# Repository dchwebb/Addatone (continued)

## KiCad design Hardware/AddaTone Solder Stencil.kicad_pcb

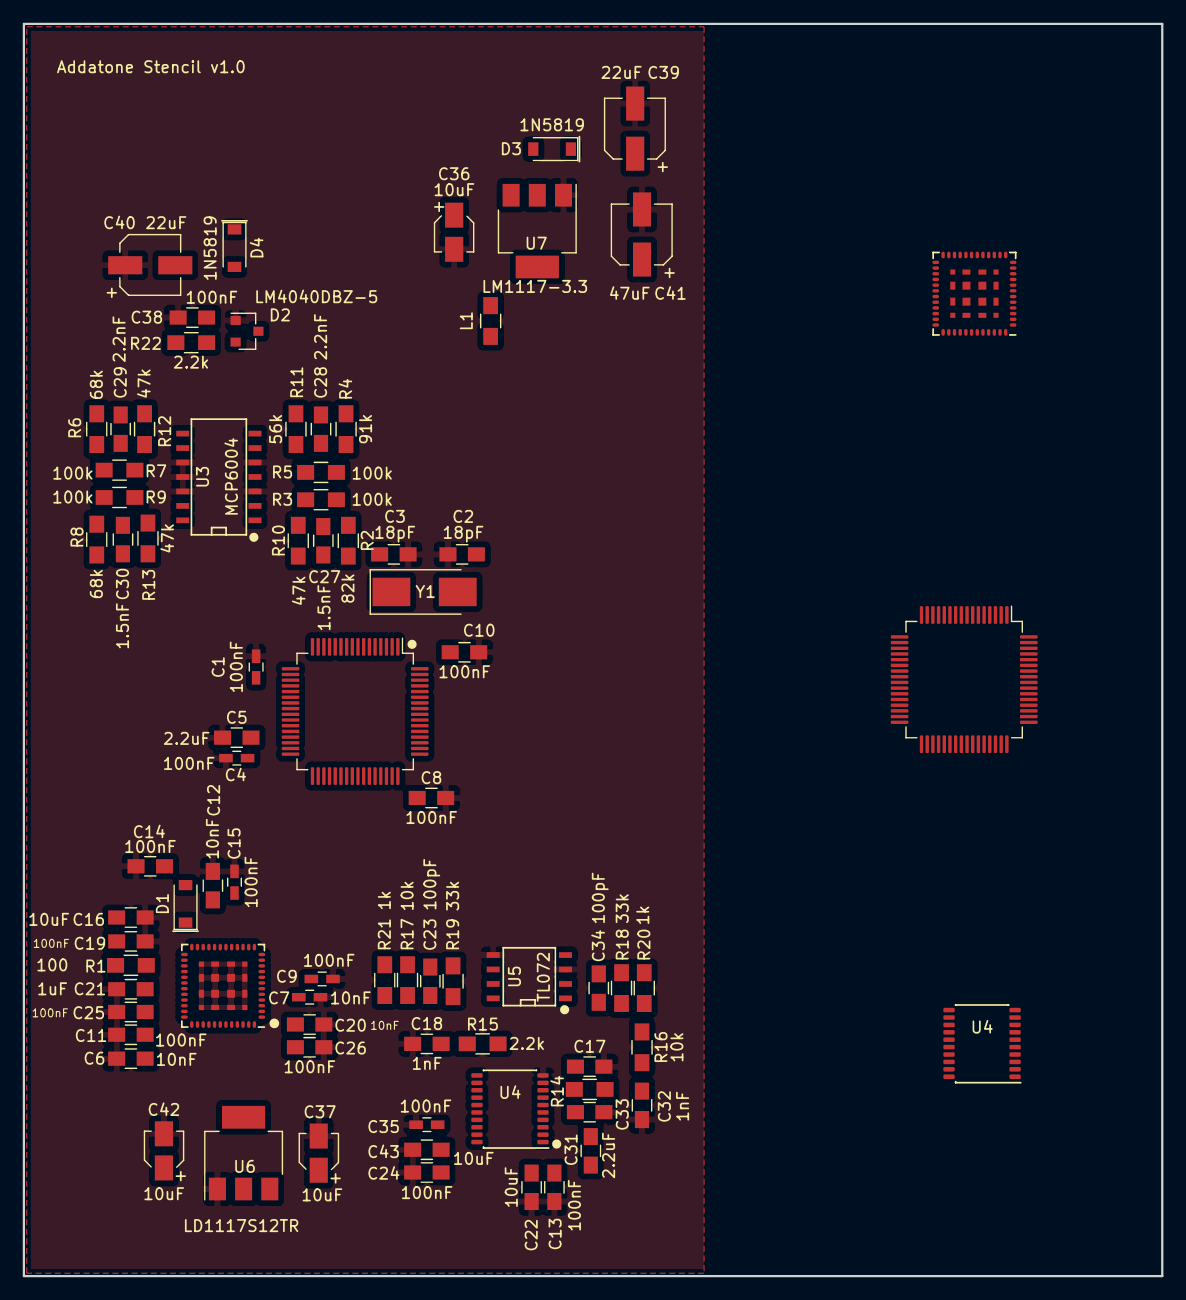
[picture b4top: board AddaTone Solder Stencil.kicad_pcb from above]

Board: 2 copper layers, 100.0 x 110.0 mm, 81 parts (0 on the bottom side), 110 nets, no tracks yet.

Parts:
C1, C4, C9, C15, C35: 100nF; C_0603_HandSoldering
C2, C3: 18pF; C_0805_HandSoldering
C5, C31, C33: 2.2uF; C_0805_HandSoldering
C6, C12, C20: 10nF; C_0805_HandSoldering
C7: 10nF; C_0603_HandSoldering
C8, C10, C11, C13, C14, C17, C19, C24, C25, C26, C38: 100nF; C_0805_HandSoldering
C16, C22, C43: 10uF; C_0805_HandSoldering
C18, C32: 1nF; C_0805_HandSoldering
C21: 1uF; C_0805_HandSoldering
C23, C34: 100pF; C_0805_HandSoldering
C27, C30: 1.5nF; C_0805_HandSoldering
C28, C29: 2.2nF; C_0805_HandSoldering
C36, C37, C42: 10uF; CP_Elec_3x5.3
C39, C40: 22uF; CP_Elec_5x5.3
C41: 47uF; CP_Elec_5x5.3
D1: MBR130T1G; D_SOD-123
D2: LM4040DBZ-5; SOT-23
D3, D4: 1N5819; D_SOD-123
L1: L; L_0805_HandSoldering
R1: 100; R_0805_HandSoldering
R2: 82k; R_0805_HandSoldering
R3, R5, R7, R9: 100k; R_0805_HandSoldering
R4: 91k; R_0805_HandSoldering
R6, R8: 68k; R_0805_HandSoldering
R10, R12, R13: 47k; R_0805_HandSoldering
R11: 56k; R_0805_HandSoldering
R14, R15, R22: 2.2k; R_0805_HandSoldering
R16, R17: 10k; R_0805_HandSoldering
R18, R19: 33k; R_0805_HandSoldering
R20, R21: 1k; R_0805_HandSoldering
U1, U1#2: STM32F446RETx; LQFP-64_10x10mm_P0.5mm
U2, U2#2: ICE40UP5K-SG48ITR; ICE40_QFN-48-stencil
U3: MCP6004; SOIC-14_N
U4, U4#2: PCM5100APW; SSOP-20_4.4x6.5mm_Pitch0.65mm_Round_Pads
U5: TL072; SOIC-8-N
U6: LD1117S12TR; SOT-223
U7: LM1117-3.3; SOT-223
Y1: ECS-12MHz; Crystal_SMD_0603-2pin_6.0x3.5mm_HandSoldering

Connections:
+1V2: C7.1, C9.1, C16.1, C19.1, C21.1, C25.1, C42.1, R1.1, U2.5, U2.30, U2#2.5, U2#2.30, U6.2
+3.3VA: C13.1, C17.1, C22.1, L1.1, U1.13, U1#2.13, U3.4, U4.1, U4.8, U4#2.1, U4#2.8
ADC_CS: U1.50, U1#2.50, U2.10, U2#2.10
ADC_Clock: U1.55, U1#2.55, U2.9, U2#2.9
ADC_Data: U1.57, U1#2.57, U2.6, U2#2.6
AREF_-5: C38.1, D2.2, R2.2, R4.2, R6.2, R8.2, R22.2
CTUNE: U1.27, U1#2.27
Calibration: U1.2, U1#2.2
DAC1_OUT: R14.2, U4.6, U4#2.6
DAC2_OUT: R15.2, U4.7, U4#2.7
DAC_BCLK: U2.4, U2#2.4, U4.13, U4#2.13
DAC_DATA: U2.3, U2#2.3, U4.14, U4#2.14
DAC_LRCLK: U2.48, U2#2.48, U4.15, U4#2.15
FPGA_DONE: U1.42, U1#2.42, U2.7, U2#2.7
FPGA_RESET: U1.38, U1#2.38, U2.8, U2#2.8
FPGA_SCK: U1.34, U1#2.34, U2.15, U2#2.15
FPGA_SI: U1.36, U1#2.36, U2.17, U2#2.17
FPGA_SO: U2.14, U2#2.14
FPGA_SS: U1.33, U1#2.33, U2.16, U2#2.16
FTUNE: U1.25, U1#2.25
F_TEST1: U2.42, U2#2.42
F_TEST2: U2.45, U2#2.45
GND: C1.2, C2.2, C3.2, C4.2, C5.1, C6.2, C7.2, C8.2, C9.2, C10.2, C11.2, C12.2, C13.2, C14.1, C15.2, C16.2, C17.2, C18.1, C19.2, C20.2, C21.2, C22.2, C24.2, C25.2, C26.2, C32.1, C33.2, C35.1, C36.2, C37.2, C38.2, C39.2, C40.1, C41.2, C42.2, C43.2, D2.1, U1.12, U1.18, U1.31, U1.47, U1.60, U1.63, U1#2.12, U1#2.18, U1#2.31, U1#2.47, U1#2.60, U1#2.63, U2.49, U2#2.49, U3.3, U3.5, U3.10, U3.11, U3.12, U4.3, U4.9, U4.10, U4.12, U4.16, U4.19, U4#2.3, U4#2.9, U4#2.10, U4#2.12, U4#2.16, U4#2.19, U5.3, U5.5, U6.1, U7.1
HARM1_CV: C28.2, R11.1, U1.11, U1#2.11, U3.7
HARM1_POT: U1.26, U1#2.26
HARM2_CV: C29.2, R12.1, U1.17, U1#2.17, U3.8
HARM2_POT: U1.10, U1#2.10
HARM_COUNT_POT: U1.16, U1#2.16
MCO2_CLOCK_OUT: U1.40, U1#2.40, U2.20, U2#2.20
MIX_SWITCH: U2.37, U2#2.37
unnamed: C2.1, U1.5, U1#2.5, Y1.2
unnamed: C3.1, U1.6, U1#2.6, Y1.1
unnamed: C5.2, U1.30, U1#2.30
unnamed: C18.2, R15.1, R17.2
unnamed: C23.1, R17.1, R19.2, U5.6
unnamed: C23.2, R19.1, R21.2, U5.7
unnamed: C27.1, R2.1, R3.1, R10.2, U3.2
unnamed: C28.1, R4.1, R5.1, R11.2, U3.6
unnamed: C29.1, R6.1, R7.1, R12.2, U3.9
unnamed: C30.1, R8.1, R9.1, R13.2, U3.13
unnamed: C31.1, U4.2, U4#2.2
unnamed: C31.2, U4.4, U4#2.4
unnamed: C32.2, R14.1, R16.2
unnamed: C33.1, U4.5, U4#2.5
unnamed: C34.1, R16.1, R18.2, U5.2
unnamed: C34.2, R18.1, R20.2, U5.1
unnamed: C35.2, U4.18, U4#2.18
unnamed: D1.1, U2.24, U2#2.24
unnamed: R1.2, U2.29, U2#2.29
unnamed: U1.1, U1#2.1
unnamed: U1.3, U1#2.3
unnamed: U1.4, U1#2.4
unnamed: U1.9, U1#2.9
unnamed: U1.14, U1#2.14
unnamed: U1.15, U1#2.15
unnamed: U1.20, U1#2.20
unnamed: U1.21, U1#2.21
unnamed: U1.24, U1#2.24
unnamed: U1.28, U1#2.28
unnamed: U1.29, U1#2.29
unnamed: U1.35, U1#2.35
unnamed: U1.37, U1#2.37
unnamed: U1.39, U1#2.39
unnamed: U1.41, U1#2.41
unnamed: U1.43, U1#2.43
unnamed: U1.44, U1#2.44
unnamed: U1.45, U1#2.45
unnamed: U1.51, U1#2.51
unnamed: U1.52, U1#2.52
unnamed: U1.53, U1#2.53
unnamed: U1.54, U1#2.54
unnamed: U1.56, U1#2.56
unnamed: U1.58, U1#2.58
unnamed: U1.59, U1#2.59
unnamed: U1.61, U1#2.61
unnamed: U1.62, U1#2.62
unnamed: U2.2, U2#2.2
unnamed: U2.11, U2#2.11
unnamed: U2.12, U2#2.12
unnamed: U2.13, U2#2.13
unnamed: U2.18, U2#2.18
unnamed: U2.19, U2#2.19
unnamed: U2.21, U2#2.21
unnamed: U2.23, U2#2.23
unnamed: U2.26, U2#2.26
unnamed: U2.27, U2#2.27
unnamed: U2.28, U2#2.28
unnamed: U2.31, U2#2.31
unnamed: U2.32, U2#2.32
unnamed: U2.34, U2#2.34
unnamed: U2.35, U2#2.35
unnamed: U2.36, U2#2.36
unnamed: U2.38, U2#2.38
unnamed: U2.39, U2#2.39
unnamed: U2.40, U2#2.40
unnamed: U2.41, U2#2.41
unnamed: U2.43, U2#2.43
unnamed: U2.44, U2#2.44
unnamed: U2.46, U2#2.46
unnamed: U2.47, U2#2.47
PITCH_CV: C27.2, R10.1, U1.22, U1#2.22, U3.1
RESET: U1.7, U1#2.7
RING_MOD: U2.25, U2#2.25
SWCLK: U1.49, U1#2.49
SWDIO: U1.46, U1#2.46
VCC: C36.1, C37.1, C39.1, D3.1, U5.8, U6.3, U7.3
VCCIO_0: C1.1, C4.1, C6.1, C8.1, C10.1, C11.1, C12.1, C14.2, C15.1, C20.1, C24.1, C26.1, C41.1, C43.1, D1.2, L1.2, U1.19, U1.32, U1.48, U1.64, U1#2.19, U1#2.32, U1#2.48, U1#2.64, U2.1, U2.22, U2.33, U2#2.1, U2#2.22, U2#2.33, U4.11, U4.17, U4.20, U4#2.11, U4#2.17, U4#2.20, U7.2
VEE: C40.2, D4.2, R22.1, U5.4
WARP_CV: C30.2, R13.1, U1.23, U1#2.23, U3.14
WARP_POT: U1.8, U1#2.8

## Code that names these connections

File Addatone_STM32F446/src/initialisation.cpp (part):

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void InitHardware()
{
	InitClocks();
	InitMCO2();									// Initialise output of HSE oscillator on pin PC9
	InitSysTick();
	InitIO();
	InitFPGAProg();								// Initialise SPI peripheral used to program bitstream into FPGA
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
void InitMCO2()
{
	// Initialise oscillator output on MCO2 pin PC9
	RCC->AHB1ENR |= RCC_AHB1ENR_GPIOCEN;
	GPIOC->MODER |= GPIO_MODER_MODER9_1;			// Set PC9 to Alternate function mode (0b10); Uses alternate function AF0 so set by default

	RCC->CFGR |= RCC_CFGR_MCO2_1; 					// 00: System clock; 01: PLLI2S clock; 10: HSE; 11: PLL clock
}
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

	/* 446:
	0	PITCH_CV		PA6
	1	HARM1_CV		PC3
	2	HARM2_CV		PA3
	3	FREQ_SCALE_CV	PA7
	4	HARM_COUNT_POT	PA2
	5	CTUNE			PB1
	6	FTUNE			PC5
	7	HARM1_POT		PB0
	8	HARM2_POT		PC2
	9	FREQ_SC_POT		PC0
	*/

	ADC2->CR1 |= ADC_CR1_SCAN;						// Activate scan mode
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	//	Enable GPIO and SPI clocks
	RCC->APB1ENR |= RCC_APB1ENR_SPI2EN;

	GpioPin::Init(GPIOB, 15, GpioPin::Type::AlternateFunction, 5, GpioPin::DriveStrength::VeryHigh);	// PB15: SPI_MOSI [alternate function AF5] to ICE_MOSI
	GpioPin::Init(GPIOB, 13, GpioPin::Type::AlternateFunction, 5, GpioPin::DriveStrength::VeryHigh);		// PB13: SPI_SCK [alternate function AF5]
	GpioPin::Init(GPIOB, 12, GpioPin::Type::Output);			// PB12 Software NSS
	GpioPin::SetHigh(GPIOB, 12);

	// PC7 Reset FPGA - configure as Open drain. This will only pull pin low when set to 0; otherwise output is high impedence
	RCC->AHB1ENR |= RCC_AHB1ENR_GPIOCEN;			// reset and clock control - advanced high performance bus - GPIO port C
	GPIOC->OTYPER |= GPIO_OTYPER_OT7;				// Configure as open drain
	GPIOC->BSRR |= GPIO_BSRR_BS_7;
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{
	RCC->APB1ENR |= RCC_APB1ENR_SPI3EN;				//	Enable SPI clock

	GpioPin::Init(GPIOB, 5, GpioPin::Type::AlternateFunction, 6, GpioPin::DriveStrength::VeryHigh);		// PB5 (57): SPI_MOSI [AF6]
	GpioPin::Init(GPIOB, 3, GpioPin::Type::AlternateFunction, 6, GpioPin::DriveStrength::VeryHigh);		// PB3 (55) SPI_SCK [AF6]
	GpioPin::Init(GPIOA, 15, GpioPin::Type::Output);													// PA15 (50) Software NSS
	GpioPin::SetHigh(GPIOA, 15);

	// Configure SPI
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void InitI2S()
{
	/* All AF5
	PC3 I2S2_SD
	PC6 I2S2_MCK
	[PC9 I2S_CKIN]

	62 PB9 I2S2_WS
	PB10 I2S2_CK
	33 PB12 I2S2_WS
	34 PB13 I2S2_CK
	[PB14 I2S2ext_SD]
	36 PB15 I2S2_SD

	*/
	//	Enable GPIO and SPI clocks
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	RCC->APB1ENR |= RCC_APB1ENR_SPI2EN;

/*
	// PB12: I2S2_WS [alternate function AF5]
	GPIOB->MODER |= GPIO_MODER_MODER12_1;			// 00: Input (reset state)	01: General purpose output mode	10: Alternate function mode	11: Analog mode
	GPIOB->OSPEEDR |= GPIO_OSPEEDER_OSPEEDR12;		// V High  - 00: Low speed; 01: Medium speed; 10: High speed; 11: Very high speed
	GPIOB->AFR[1] |= 0b0101 << 16;					// 0b0101 = Alternate Function 5 (I2S2); 16 is position of Pin 12
*/

	// PB9: I2S2_WS [alternate function AF5]
	GPIOB->MODER |= GPIO_MODER_MODER9_1;			// 00: Input (reset state)	01: General purpose output mode	10: Alternate function mode	11: Analog mode
	GPIOB->AFR[1] |= 0b0101 << 4;					// 0b0101 = Alternate Function 5 (I2S2); 4 is position of Pin 9

	// PB13 I2S2_CK [alternate function AF5]
	GPIOB->MODER |= GPIO_MODER_MODER13_1;			// 00: Input (reset state)	01: General purpose output mode	10: Alternate function mode	11: Analog mode
	//GPIOB->OSPEEDR |= GPIO_OSPEEDER_OSPEEDR13;		// V High  - 00: Low speed; 01: Medium speed; 10: High speed; 11: Very high speed
	GPIOB->AFR[1] |= 0b0101 << 20;					// 0b0101 = Alternate Function 6 (I2S2); 20 is position of Pin 13

	// PB15 I2S2_SD [alternate function AF5]
	GPIOB->MODER |= GPIO_MODER_MODER15_1;			// 00: Input (reset state)	01: General purpose output mode	10: Alternate function mode	11: Analog mode
	//GPIOB->OSPEEDR |= GPIO_OSPEEDER_OSPEEDR15;		// V High  - 00: Low speed; 01: Medium speed; 10: High speed; 11: Very high speed
	GPIOB->AFR[1] |= 0b0101 << 28;					// 0b0101 = Alternate Function 6 (I2S2); 28 is position of Pin 15
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
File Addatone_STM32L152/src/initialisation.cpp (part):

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	RCC->AHBENR |= RCC_AHBENR_GPIOBEN;
	RCC->APB2ENR |= RCC_APB2ENR_ADC1EN;

	// Enable ADC - PB0: IN8;
	GPIOB->MODER |= GPIO_MODER_MODER0;				// Set PB0 to Analog mode (0b11)

	ADC1->SQR5 |= 8 << 0;							// Set IN8  1st conversion in sequence

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	RCC->APB2ENR |= RCC_APB2ENR_ADC1EN;

	/* 446:
	PC0 ADC123_IN10
	PC1 ADC123_IN11
	PC2 ADC123_IN12
	PC3 ADC123_IN13
	PC4 ADC123_IN14
	PC5 ADC123_IN15

	PA0 ADC123_IN0
	PA1 ADC123_IN1
	PA2 ADC123_IN2
	PA3 ADC123_IN3
	PA4 ADC12_IN4
	PA5 ADC12_IN5
	PA6 ADC12_IN6
	PA7 ADC12_IN7

	PB0 ADC12_IN8
	PB1 ADC12_IN9
	*/

	// Enable ADC - Set Pins to Analog mode (0b11)
	GPIOA->MODER |= GPIO_MODER_MODER0;				// Set PA0 ADC_IN0
	GPIOA->MODER |= GPIO_MODER_MODER1;				// Set PA1 ADC_IN1
	GPIOA->MODER |= GPIO_MODER_MODER2;				// Set PA2 ADC_IN2
	GPIOA->MODER |= GPIO_MODER_MODER3;				// Set PA3 ADC_IN3
	GPIOA->MODER |= GPIO_MODER_MODER4;				// Set PA4 ADC_IN4
	GPIOA->MODER |= GPIO_MODER_MODER5;				// Set PA5 ADC_IN5
	GPIOA->MODER |= GPIO_MODER_MODER6;				// Set PA6 ADC_IN6 *** Not Working
	GPIOA->MODER |= GPIO_MODER_MODER7;				// Set PA7 ADC_IN7

	GPIOB->MODER |= GPIO_MODER_MODER0;				// Set PB0 ADC_IN8
	GPIOB->MODER |= GPIO_MODER_MODER1;				// Set PB1 ADC_IN9 *** Not working

	GPIOB->MODER |= GPIO_MODER_MODER12;				// Set PB12 ADC_IN18
	GPIOB->MODER |= GPIO_MODER_MODER13;				// Set PB13 ADC_IN19 *** Not Working
	GPIOB->MODER |= GPIO_MODER_MODER14;				// Set PB14 ADC_IN20 *** Not Working
	GPIOB->MODER |= GPIO_MODER_MODER15;				// Set PB15 ADC_IN21

	ADC1->CR1 |= ADC_CR1_SCAN;						// Activate scan mode
	ADC1->SQR1 = (ADC_BUFFER_LENGTH - 1) << 20;		// Number of conversions in sequence
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	RCC->AHBENR |= RCC_AHBENR_GPIOBEN;			// reset and clock control - advanced high performance bus - GPIO port B
	RCC->APB2ENR |= RCC_APB2ENR_SPI1EN;

	// PB5 (57): SPI_MOSI [alternate function AF5]
	GPIOB->MODER |= GPIO_MODER_MODER5_1;			// 00: Input (reset state)	01: General purpose output mode	10: Alternate function mode	11: Analog mode
	GPIOB->OSPEEDR |= GPIO_OSPEEDER_OSPEEDR5;		// V High  - 00: Low speed; 01: Medium speed; 10: High speed; 11: Very high speed
	GPIOB->AFR[0] |= 0b0101 << 20;					// 0b0110 = Alternate Function 5 (SPI1); 20 is position of Pin 5

	// PB3 (55) SPI_SCK [alternate function AF5]
	GPIOB->MODER &= ~GPIO_MODER_MODER3;				// Reset value of PB3 is 0b10
	GPIOB->MODER |= GPIO_MODER_MODER3_1;			// 00: Input (reset state)	01: General purpose output mode	10: Alternate function mode	11: Analog mode
	GPIOB->OSPEEDR |= GPIO_OSPEEDER_OSPEEDR3;		// V High  - 00: Low speed; 01: Medium speed; 10: High speed; 11: Very high speed
	GPIOB->AFR[0] |= 0b0101 << 12;					// 0b0110 = Alternate Function 5 (SPI1); 12 is position of Pin 3

	// PA15 (50) Software NSS
	GPIOA->MODER |= GPIO_MODER_MODER15_0;			// 00: Input (reset state)	01: General purpose output mode	10: Alternate function mode	11: Analog mode
	GPIOA->MODER &= ~GPIO_MODER_MODER15_1;
	GPIOA->BSRR |= GPIO_BSRR_BS_15;
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
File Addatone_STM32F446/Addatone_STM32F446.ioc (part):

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Mcu.Name=STM32F446Z(C-E)Tx
Mcu.Package=LQFP144
Mcu.UserName=STM32F446ZETx
PA10.GPIOParameters=GPIO_Label
PA10.GPIO_Label=USB_ID
PA10.Signal=USB_OTG_FS_ID
PA11.GPIOParameters=GPIO_Label
PA11.GPIO_Label=USB_DM
PA11.Signal=USB_OTG_FS_DM
PA12.GPIOParameters=GPIO_Label
PA12.GPIO_Label=USB_DP
PA12.Signal=USB_OTG_FS_DP
PA13.GPIOParameters=GPIO_Label
PA13.GPIO_Label=TMS
PA13.Signal=SYS_JTMS-SWDIO
PA14.GPIOParameters=GPIO_Label
PA14.GPIO_Label=TCK
PA14.Signal=SYS_JTCK-SWCLK
PA8.GPIOParameters=GPIO_Label
PA8.GPIO_Label=USB_SOF [TP1]
PA8.Signal=USB_OTG_FS_SOF
PA9.GPIOParameters=GPIO_Label
PA9.GPIO_Label=USB_VBUS
PA9.Signal=USB_OTG_FS_VBUS
PB0.GPIOParameters=GPIO_Label
PB0.GPIO_Label=LD1 [Green]
PB0.Signal=GPIO_Output
PB10.Mode=Half_Duplex_Master
PB10.Signal=I2S2_CK
PB12.Mode=Half_Duplex_Master
PB12.Signal=I2S2_WS
PB14.GPIOParameters=GPIO_Label
PB14.GPIO_Label=LD3 [Red]
PB14.Signal=GPIO_Output
PB7.GPIOParameters=GPIO_Label
PB7.GPIO_Label=LD2 [Blue]
PB7.Signal=GPIO_Output
PC1.Mode=Half_Duplex_Master
PC1.Signal=I2S2_SD
PC13.GPIOParameters=GPIO_Label
PC13.GPIO_Label=USER_Btn [B1]
PC13.Signal=GPXTI13
PC14-OSC32_IN.Signal=RCC_OSC32_IN
PC15-OSC32_OUT.Signal=RCC_OSC32_OUT
PC9.Mode=Clock-out-2
PC9.Signal=RCC_MCO_2
PD8.GPIOParameters=GPIO_Label
PD8.GPIO_Label=STLK_RX [STM32F103CBT6_PA3]
PD8.Signal=USART3_TX
PD9.GPIOParameters=GPIO_Label
PD9.GPIO_Label=STLK_TX [STM32F103CBT6_PA2]
PD9.Signal=USART3_RX
PG6.GPIOParameters=GPIO_Label
PG6.GPIO_Label=USB_PowerSwitchOn [STMPS2151STR_EN]
PG6.Signal=GPIO_Output
PG7.GPIOParameters=GPIO_Label
PG7.GPIO_Label=USB_OverCurrent [STMPS2151STR_FAULT]
PG7.Signal=GPIO_Input
PH0-OSC_IN.GPIOParameters=GPIO_Label
PH0-OSC_IN.GPIO_Label=MCO [STM32F103CBT6_PA8]
PH0-OSC_IN.Mode=HSE-External-Oscillator
PH0-OSC_IN.Signal=RCC_OSC_IN
PH1-OSC_OUT.Mode=HSE-External-Oscillator
PH1-OSC_OUT.Signal=RCC_OSC_OUT
RCC.HSE_VALUE=12000000
RCC.SYSCLKFreq_VALUE=144000000
RCC.SYSCLKSource=RCC_SYSCLKSOURCE_PLLCLK
RCC.SYSCLKSourceVirtual=RCC_SYSCLKSOURCE_PLLCLK
board=NUCLEO-F446ZE
boardIOC=true

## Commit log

2020-02-09 Implemented basic state machine for harmonic generation
2020-02-10 Added fractional adder module
2020-02-10 Fractional Adder Fiunctional
2020-02-11 Pseudo saw wave implemented
2020-02-11 Sample Position Array now referenced directly from harmonic number
2020-02-11 Code clean up
2020-02-11 tweaks to resolve timing errors (main loop uses single state machine)
2020-02-12 Further performance tweaks to state machine
2020-02-13 New STM32L152 and 451 dev board
    Reorganised ARM project to use later CMSIS libraries; Reorganised FPGA project to move verilog files to source folder; started troubleshooting frequency errors when potentiometer input values high
2020-02-14 Refactored ADC code
2020-02-14 Added further error handling to ADC
2020-02-14 ADC now stable with 2x16bit input values
2020-02-14 Dev Board 1.1 layout finalised and gerbers sent to manufacturing
2020-02-23 Removed asynchronous resets
2020-02-23 Fixes to sample LUT calculations
2020-02-24 Cleaned up state machine
2020-02-24 First draft of Sample Position module (not yet integrated in main)
2020-02-24 Moved sample position calculation to separate module to reduce overall sample calculation time
2020-02-26 Changes to use sample position lookup; tidied up top state machine
2020-02-26 Added javascript tool to graphically assist with sample positioning to reduce crest factor
2020-02-28 Added ARM I2S implementation to test potentially faulty DAC
2020-02-29 Updated sample position LUT tool to scale and export results for use in FPGA RAM
2020-02-29 Added buld script and optimised sample position lookup
2020-03-01 Refactored sample position module to combine sample position and sine LUT lookup
2020-03-01 Created separate module for scaling harmonic multiplier; refactoring
2020-03-02 (Yet another) rewrite of ADC module to handle noise better
2020-03-04 Harmonic Scaling Updates
    - MCU passes scaled attenuation level to provide smoother transition across range of control (ie linear to exponential scaling)
    - MCU passes initial level of harmonics, reducing overall level as number of harmonics increases
    - Updates to FPGA code to properly parameterise length of attenuation variables and allow passing of initial level to scale multiplier module
2020-03-04 Added additional ADC channel for controlling harmonic level from CV
2020-03-05 Added second adder module with some refactoring
2020-03-06 Added Sample Output module to handle sending stereo outs
2020-03-09 Lots of work on CV damping, better CV resolution and volume auto-levelling
2020-03-10 Iniitial setup for frequency scaling
2020-03-11 Frequency Scaling implemented (Issue where FPGA has no output until reset)
2020-03-11 Tweaks to partially handle issues when frequency offset level is too low
2020-03-11 Performance tweaks to offset mechanism; refactoring
2020-03-12 Variable and State Machine refactoring
2020-03-13 Added additional ADC Channel with macros for simplified configuration
2020-03-13 Preparing to add comb filter control
2020-03-13 Refactoring adder controls
2020-03-13 Basic comb filtering implemented
2020-03-17 Transferred ADC MCU to STM32L152; tweaks to comb filtering
2020-03-23 Added early draft of support for ICE40UP5k FPGA
2020-03-23 Mach X03 codebase transferred though not yet working
2020-03-24 ICE40 implementation partially working; adder rewritten to use hardware multiplier
2020-03-25 Fixed bug in Adder causing polarity of fundamental to flip
2020-03-26 Clean up top state machine
2020-03-26 Replaced IP PLL wrapper with custom one to remove warnings
2020-03-26 Removing report files
2020-03-26 Added ADC support for separate even harmonic scaler
2020-03-26 Separate Even/Odd scaler plumbing
2020-03-26 Even/Odd scaler working
2020-03-28 Improved resolution of harmonic scale; Fixed issues with frequency scaling
2020-03-28 Added control for selecting number of harmonics before scaling
2020-03-29 Use arithmetic shift in Adder
2020-03-29 Added STM32F446 project to test programming FPGA from microcontroller
2020-03-30 Successfully implemented FPGA programming from Microcontroller
2020-03-31 Fixed issue in programmer where clock polarity setting was affecting slave select signal
    Also added preliminary work to compress bitstream by encoding repeated zeros
2020-04-03 Rev 2 of dev board; provisional handling for overflow on output samples
2020-04-03 Cleaned sample output module and reduced sample register size to 24 bits
2020-04-03 Added provisional mix option to Sample_out module
2020-04-04 Implemented Mix switch
2020-04-06 Implemented separate ring mod and mix settings for left and right channels
    Varioud tweaks to work around timing errors
2020-04-07 Tweaks to remove warnings and work around ongoing timing issues
2020-04-09 Updates to schematic
2020-04-10 Updated schematic for PCM5100 DAC
2020-04-11 Started laying out PCB
2020-04-14 Initial PCB Wiring Completed
2020-04-15 Updated microcontroller code for correct ADC channels and implemented HSE oscillator output
2020-04-16 Minor tweaks to PCB layout
2020-04-16 Rough layout of controls PCB
2020-04-17 Further refinements to PCB layout
2020-04-18 Refinements to PCB
2020-04-19 First draft of Panel PCB
2020-04-21 Further updates to PCBs
2020-04-21 Checking FPGA programming code and updated bitstream
2020-04-21 Updated FPGA programming code to use correct pin for Reset; Minor PCB corrections
2020-04-23 I2S Tests updated to work on STM32F446; started added IP based multiplier for Ring Mod
2020-04-29 Switched FPGA output to I2S DAC
2020-05-15 Updates to PCB layout
2020-06-01 Fixes to schematic (missing resistor on 1.2V LDO); Created new implementation to support production board; added FPGA tester project
2020-06-02 Updated MCU Code to handle fine tune and octave controls
2020-06-03 Implemented support for harmonic and warp potentiometers
2020-06-03 Updated FPGA constraints to use correct I2S pin names
2020-06-04 Fixed direction of Harmonic Count potentiometer and scaled results exponentially
2020-06-16 Updated harmonic scaling so that both potentiometer and CV can reach full scale
2021-09-21 Switch octave and fine tune controls
2021-09-21 Code cleanup
2021-09-21 Updated the code to use the warp CV input to control the number of harmonics
2021-09-22 Updated panel; altered controls to use CV to adjust harmonic count
    RTL altered to half level of last harmonic to smooth harmonic count CV control
2021-09-23 Clean up panel pcb
2021-09-23 Revised panel gerbers ready for manufacture
2022-03-11 Updated pcb files to Kicad 6.0
2024-01-15 Updating component schematic and PCB to Kicad 7.09
2024-01-16 Updated schematic and pcb to v2.1
2024-05-26 Changed gitignore to include elf file
2024-08-25 Updated firmware to support calibration
2024-08-25 Added option to clear config at startup
    Updated documentation
